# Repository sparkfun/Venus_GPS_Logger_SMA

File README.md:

SparkFun Venus GPS Logger - SMA Connector
=========================================

![SparkFun Venus GPS Logger - SMA Connector
](https://cdn.sparkfun.com//assets/parts/6/0/5/3/10920-01a.jpg)

[*SparkFun Venus GPS Logger - SMA Connector (GPS-10920)*](https://www.sparkfun.com/products/10920)

This is a breakout board for the Venus638FLPx chip. It can be configured up to 20Hz update rate. This has an on-board JST connector for battery
power and an SMA connector for an antenna. This unit supports external SPI flash memory data logging, and has the 32M Serial Flash Memory IC.

Repository Contents
-------------------
* **/Hardware** - All Eagle design files (.brd, .sch)
* **/Production** - Test bed files and production panel files

Documentation
--------------
* **[SparkFun Fritzing repo](https://github.com/sparkfun/Fritzing_Parts)** - Fritzing diagrams for SparkFun products.
* **[SparkFun 3D Model repo](https://github.com/sparkfun/3D_Models)** - 3D models of SparkFun products. 

License Information
-------------------

This product is _**open source**_! 

Please review the LICENSE.md file for license information. 

If you have any questions or concerns on licensing, please contact techsupport@sparkfun.com.

Distributed as-is; no warranty is given.

- Your friends at SparkFun.

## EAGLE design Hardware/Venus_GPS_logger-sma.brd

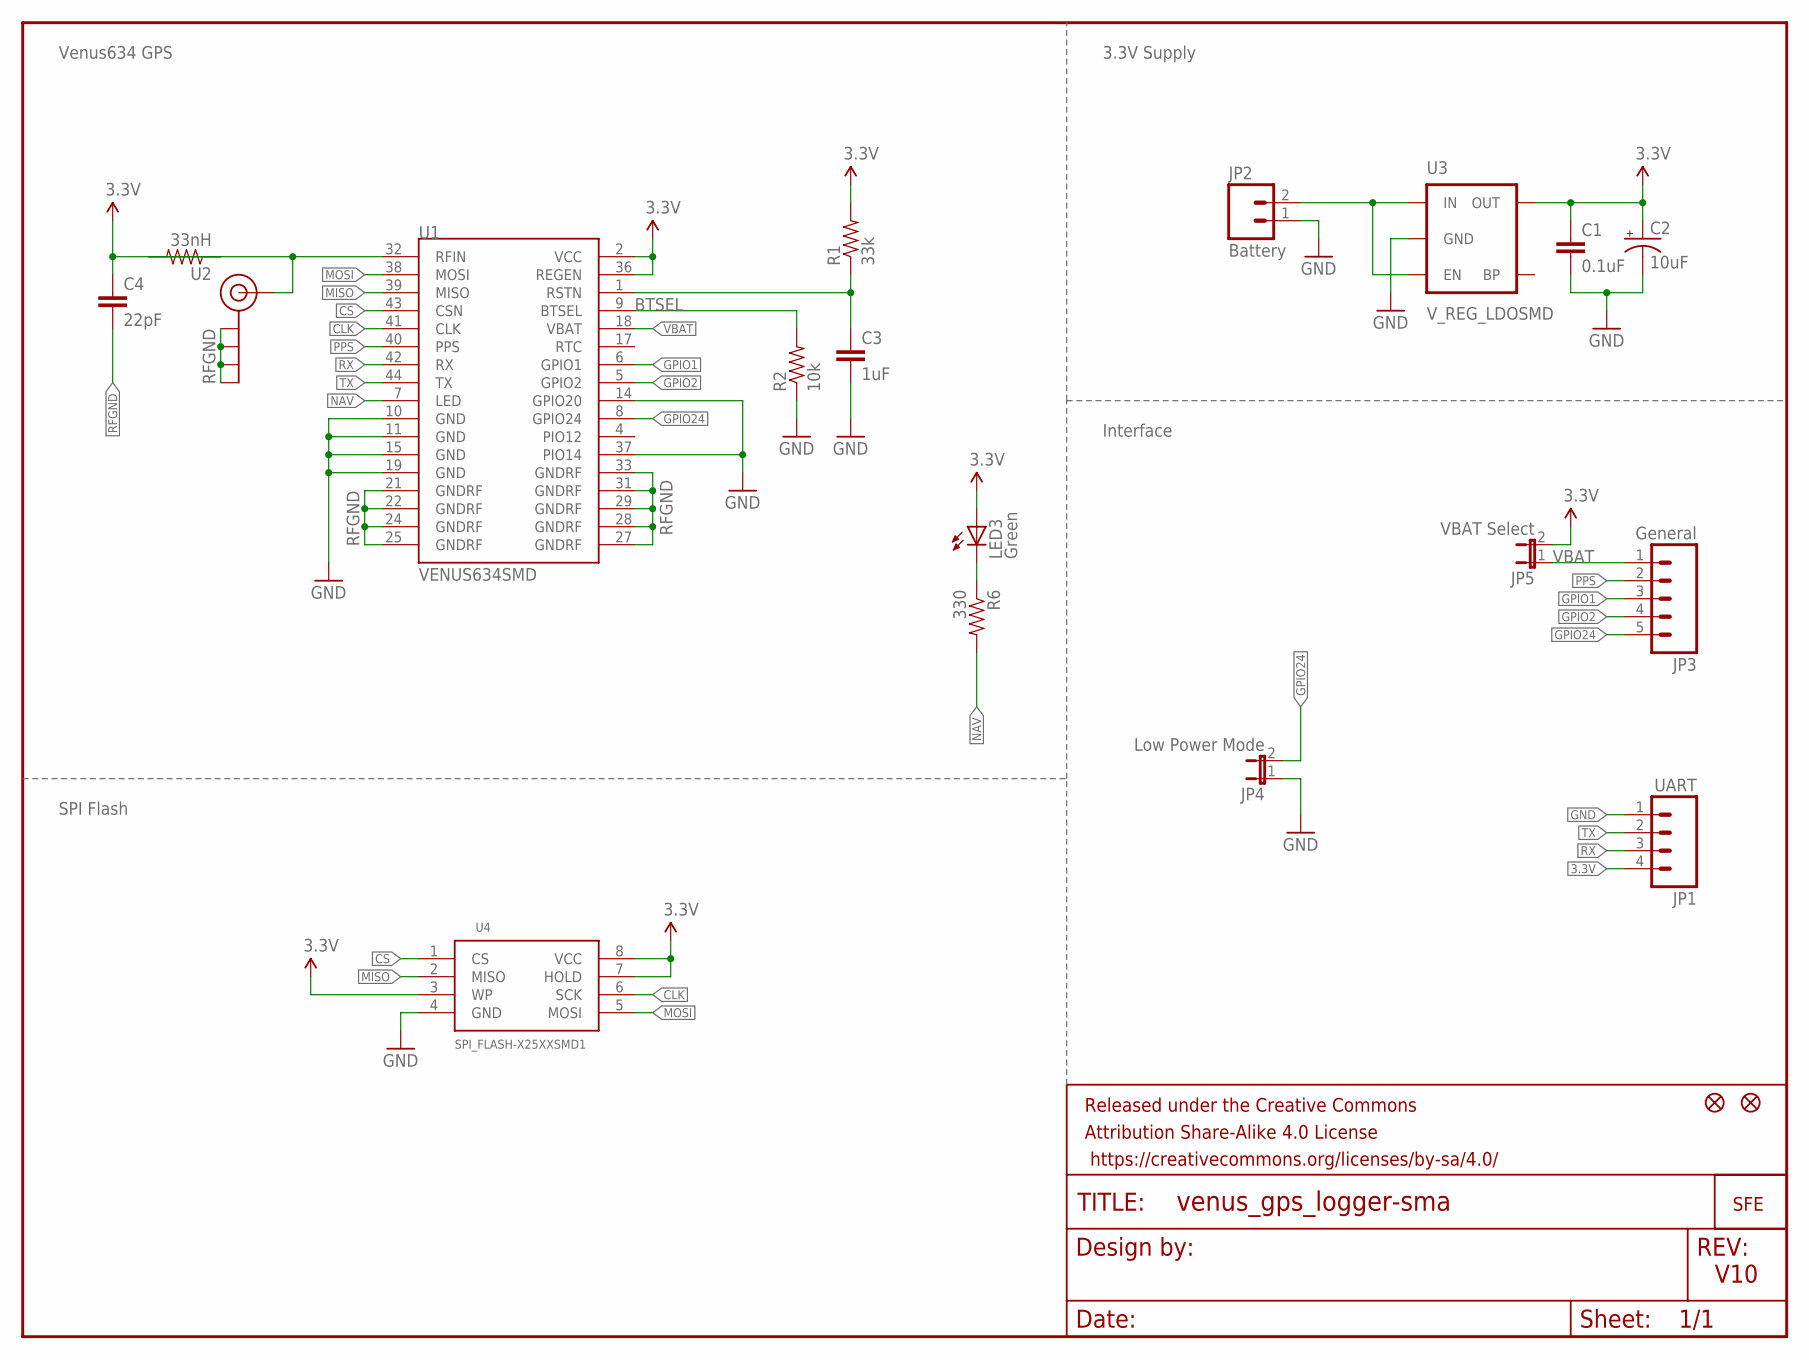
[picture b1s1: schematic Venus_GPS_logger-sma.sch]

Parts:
C1: 0.1uF; 0603-CAP
C2: 10uF; EIA3216
C3: 1uF; 0603-CAP
C4: 22pF; 0603-CAP
FRAME1: FRAME-LETTER; CREATIVE_COMMONS
J$1: SMA_EDGE; SMA-EDGE
JP1: UART; 1X04
JP2: Battery; S2B-PH
JP3: General; 1X05
JP4: Low Power Mode; SJ_2S
JP5: VBAT Select; SJ_2S
JP6, JP7: FIDUCIAL1X2.5; FIDUCIAL-1X2.5
LED3: Green; LED-0603
R1: 33k; 0603-RES
R2: 10k; 0603-RES
R6: 330; 0603-RES
U1: VENUS634SMD; LGA44
U2: 33nH; 0603-RES
U3: V_REG_LDOSMD; SOT23-5
U4: SPI_FLASH-X25XXSMD1; SO08-EIAJ
U$1: LOGO-SFESK; SFE-LOGO-FLAME

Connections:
3.3V: C1.1, C2.A (+), C4.1, JP1.4, JP5.2, LED3.A, R1.2, U1.2 (VCC), U1.36 (REGEN), U2.1, U3.5 (OUT), U4.3 (WP), U4.7 (HOLD), U4.8 (VCC)
BTSEL: R2.2, U1.9 (BTSEL)
CLK: U1.41 (CLK), U4.6 (SCK)
CS: U1.43 (CSN), U4.1 (CS)
GND: C1.2, C2.C (-), C3.2, JP1.1, JP2.1, JP4.1, R2.1, U1.10 (GND), U1.11 (GND), U1.14 (GPIO20), U1.15 (GND), U1.19 (GND), U1.37 (PIO14), U3.2 (GND), U4.4 (GND)
GPIO1: JP3.3, U1.6 (GPIO1)
GPIO2: JP3.4, U1.5 (GPIO2)
GPIO24: JP3.5, JP4.2, U1.8 (GPIO24)
MISO: U1.39 (MISO), U4.2 (MISO)
MOSI: U1.38 (MOSI), U4.5 (MOSI)
unnamed: LED3.C, R6.1
unnamed: C3.1, R1.1, U1.1 (RSTN)
unnamed: J$1.SIG (SIGNAL), U1.32 (RFIN), U2.2
NAV: R6.2, U1.7 (LED)
PPS: JP3.2, U1.40 (PPS)
RFGND: C4.2, J$1.GND@0 (GND), J$1.GND@1 (GND), J$1.GND@2 (GND), J$1.GND@3 (GND), U1.21 (GNDRF), U1.22 (GNDRF), U1.24 (GNDRF), U1.25 (GNDRF), U1.27 (GNDRF), U1.28 (GNDRF), U1.29 (GNDRF), U1.31 (GNDRF), U1.33 (GNDRF)
RX: JP1.3, U1.42 (RX)
TX: JP1.2, U1.44 (TX)
VBAT: JP3.1, JP5.1, U1.18 (VBAT)
VBATT: JP2.2, U3.1 (IN), U3.3 (EN)

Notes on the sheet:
SPI Flash
Venus634 GPS
3.3V Supply
Interface
V10

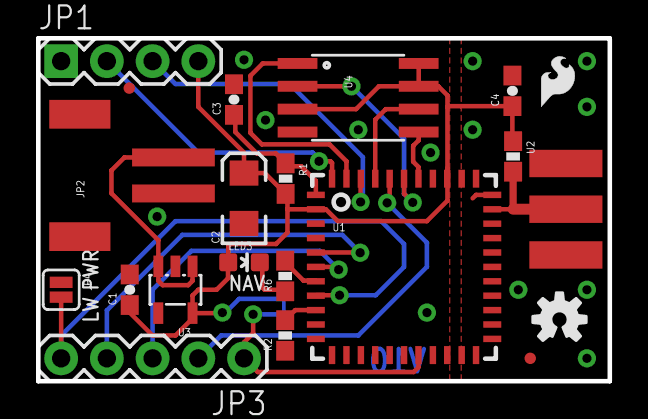
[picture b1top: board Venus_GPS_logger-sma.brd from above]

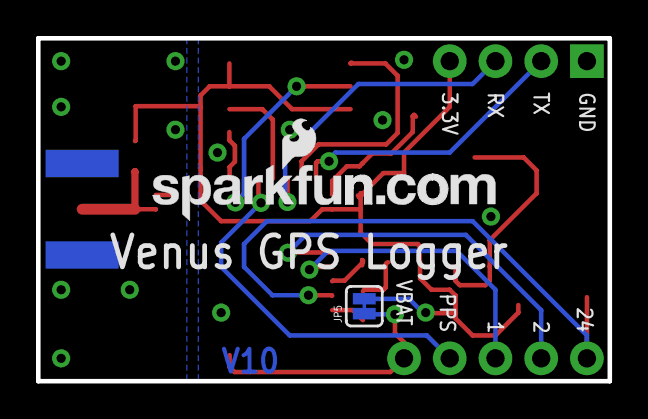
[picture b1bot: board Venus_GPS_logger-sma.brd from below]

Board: 2 copper layers, 31.8 x 19.1 mm, 24 parts (2 on the bottom side), 20 nets.

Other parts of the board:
U$2: OSHW-LOGO-S
U$3: SFE-NEW-WEBLOGO

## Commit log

2014-03-04 intial commit
    complete with BRD/SCH
2014-03-05 Wrong BRD/SCH
    the wrong files were uploaded, uploading new files.
2014-03-05 Updated caps/res/headers/jumpers
    upgraded to 0603 for all caps and res
    new tighter jumpers
    trace re routes
    added oshw logo
    added version #
    updated headers to have wider annular rings.
2014-03-07 Updated LED, fixed questionable trace routes
2014-03-18 Moved Jumper
    Moved jumper to the bttm copper, and changed silk on the jpm to "low
    power".
2014-03-18 Closed jumper
2014-04-18 changed fiducials to regular size and repositioned
2014-04-18 created panel
2014-08-07 Updating to original Eagle files
2014-08-07 Adding back in new revision files
2014-08-07 Updating readme
2015-12-02 Updating README with new product info, fixing file names ;

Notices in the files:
parts and their libraries:
SparkFun-Passives: Licensing: Creative Commons ShareAlike 4.0 International - https://creativecommons.org/licenses/by-sa/4.0
SparkFun-Aesthetics: Released under the Creative Commons Attribution Share-Alike 4.0 License
SparkFun-Aesthetics: https://creativecommons.org/licenses/by-sa/4.0
